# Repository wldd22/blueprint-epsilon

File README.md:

# Epsilon
Columnar split keyboard with 5 columns, 4 rows, and thumb clusters. Made for [Hackclub's Blueprint](https://blueprint.hackclub.com/)

## Details
PCB made using KiCAD \
Case made using Fusion360 \
Firmware made using ZMK

## About
I've always wanted to use a split keyboard, and after making a macropad, I decided the next step was to make a bigger keyboard that could actually replace my regular one for at least some daily use.

## Images

### CAD

### Schematic

### PCB

### Case
| Left Side | Right Side |
|-|-|
|  |  |

## BOM

| Item                                  | Description                                  | Quantity         | Source                                                                                                                                                          | Cost        | Amount                   |
| ------------------------------------- | -------------------------------------------- | ---------------- | --------------------------------------------------------------------------------------------------------------------------------------------------------------- | ----------- | ------------------------ |
| JLC PCB                               | Left and right sides in one piece            | 1                | JLCPCB                                                                                                                                                          | $15.30      | $15.30                   |
| JLC shipping                          | UPS Worldwide Express Saver                  | -                | -                                                                                                                                                               | -           | $15.67                   |
| Case (shipping only)                  | Left and right sides separately              | 2                | Printing Legion                                                                                                                                                 | -           | ~$5                      |
| Kalih Hotswap Sockets                 | Hotswap sockets for Choc V1 switches (x10)   | 5 (44 + 6 extra) | [Chosfox](https://chosfox.com/products/kailh-choc-switch-1350-hot-swap-sockets)                                                                                 | $1.45       | $7.25                    |
| Kailh Choc Low Profile Switches       | Kalih Choc Brown Switches (Tactile) (x10)    | 5 (44 + 6 extra) | [Chosfox](https://chosfox.com/products/kailh-chocs?variant=42514647646402)                                                                                      | $4.5        | $22.50                   |
| Chosfox shipping                      | Standard Shipping China Post                 | -                | -                                                                                                                                                               | -           | $5.20                    |
| CFX Choc Keycaps                      | Chocfox CFX Choc Blank Keycaps (Black) (x10) | 5 (44 + 6 extra) | [NeoMacro](https://typeractive.xyz/products/mbk-keycaps?variant=48512019562727)                                                                                 | ₹350        | ₹1750 (free shipping)    |
| SK6812 MINI-E RGB                     | RGB LEDs (x50)                               | 1 (44 + 6 extra) | [Desertcart](https://www.desertcart.in/products/713547616-50pcs-sk6812-mini-e-rgb-similar-with-ws2812b-sk6812-3228)                                             | ₹1219       | ₹1219 (free shipping)    |
| Seeed Studio XIAO nRF52840            | Microcontroller                              | 2                | [ThinkRobotics](https://thinkrobotics.com/products/seeed-studio-xiao-nrf52840)                                                                                  | ₹1419.93    | ₹2839.86 (free shipping) |
| 1N4148 Diodes                         | 1N4148W SOD-123 Diodes                       | 44               | [Robu](https://robu.in/product/1n4148w-sod-123-1206-diodereel-of-3000/)                                                                                         | ₹0.57 (10+) | ₹25.08                   |
| AC0805FR-072ML-YAGEO                  | 2MΩ Resistor                                 | 2                | [Robu](https://robu.in/product/ac0805fr-072ml-yageo-res-thick-film-0805-2m-ohm-1-0-125w1-8w-%C2%B1100ppm-c-pad-smd-t-r-automotive-aec-q200/)                    | ₹0.64       | ₹1.28                    |
| RT0805FRE071ML-YAGEO                  | 1MΩ Resistor                                 | 2                | [Robu](https://robu.in/product/rt0805fre071ml-yageo-125mw-thin-film-resistor-%C2%B150ppm-%E2%84%83-%C2%B11-1m%CF%89-0805-chip-resistor-surface-mount-rohs/)     | ₹1.38       | ₹2.76                    |
| Battery Jack                          | Black                                        | 2                | [Robu](https://robu.in/product/s2b-ph-klfsn-jst-1x2p-2p-ph-tin-2-25%E2%84%8385%E2%84%83-2a-1-2mm-brass-bend-insert-push-pullp2mm-wire-to-board-connector-rohs/) | ₹13         | ₹26                      |
| LiPo Battery                          | WLY752530 3.7V 500mAh 1S                     | 2                | [Robu](https://robu.in/product/500mah-pcm-protected-micro-li-po-battery/)                                                                                       | ₹261        | ₹522                     |
| Robu shipping                         | Standard Shipping                            | -                | -                                                                                                                                                               | -           | ₹49                      |
| 40x1 Pin 2.54mm Pitch Male Berg Strip | 40pin header                                 | 1                | [Robocraze](https://robocraze.com/products/40x1-pin-2-54mm-pitch-male-berg-strip)                                                                               | ₹6          | ₹6                       |
| Robocraze shipping                    | Standard                                     | -                | -                                                                                                                                                               | -           | ₹49                      |
| M2 Screws                             | Stainless steel, 8mm                         | 4                | [StacksKB](https://stackskb.com/store/m2-screw-8mm-stainless-steel/)                                                                                            | ₹3.10       | ₹12.40                   |
| M2 Hex Nuts                           | Stainless steel                              | 4                | [StacksKB](https://stackskb.com/store/m2-hex-nut-stainless-steel/)                                                                                              | ₹5          | ₹20                      |
| StacksKB shipping                     | Standard                                     | -                | -                                                                                                                                                               | -           | ₹130                     |
| **TOTAL**                             |                                              |                  |                                                                                                                                                                 |             | **~$141**                |

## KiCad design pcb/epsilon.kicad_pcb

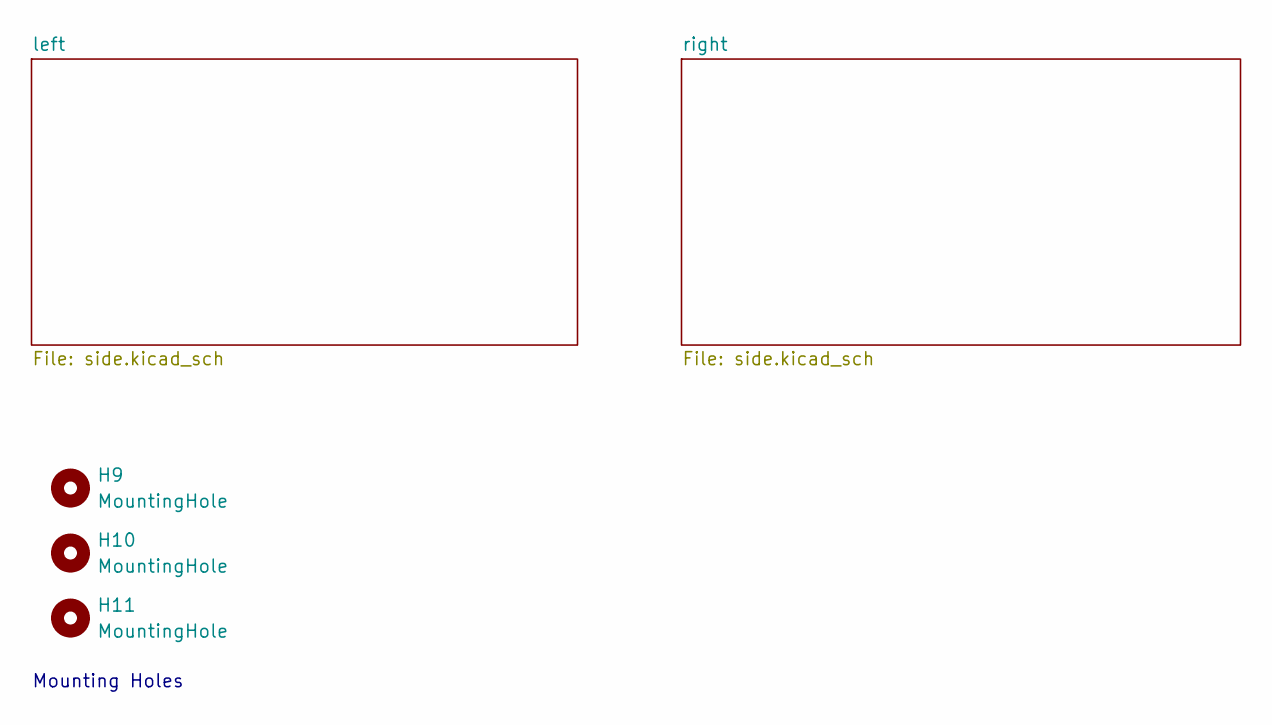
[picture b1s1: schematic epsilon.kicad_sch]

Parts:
H9, H10, H11: MountingHole; MouseBite-Slot_2.0x2.0mm_outset_D0.5mm_P0.85mm_3h

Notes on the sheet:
Mounting Holes

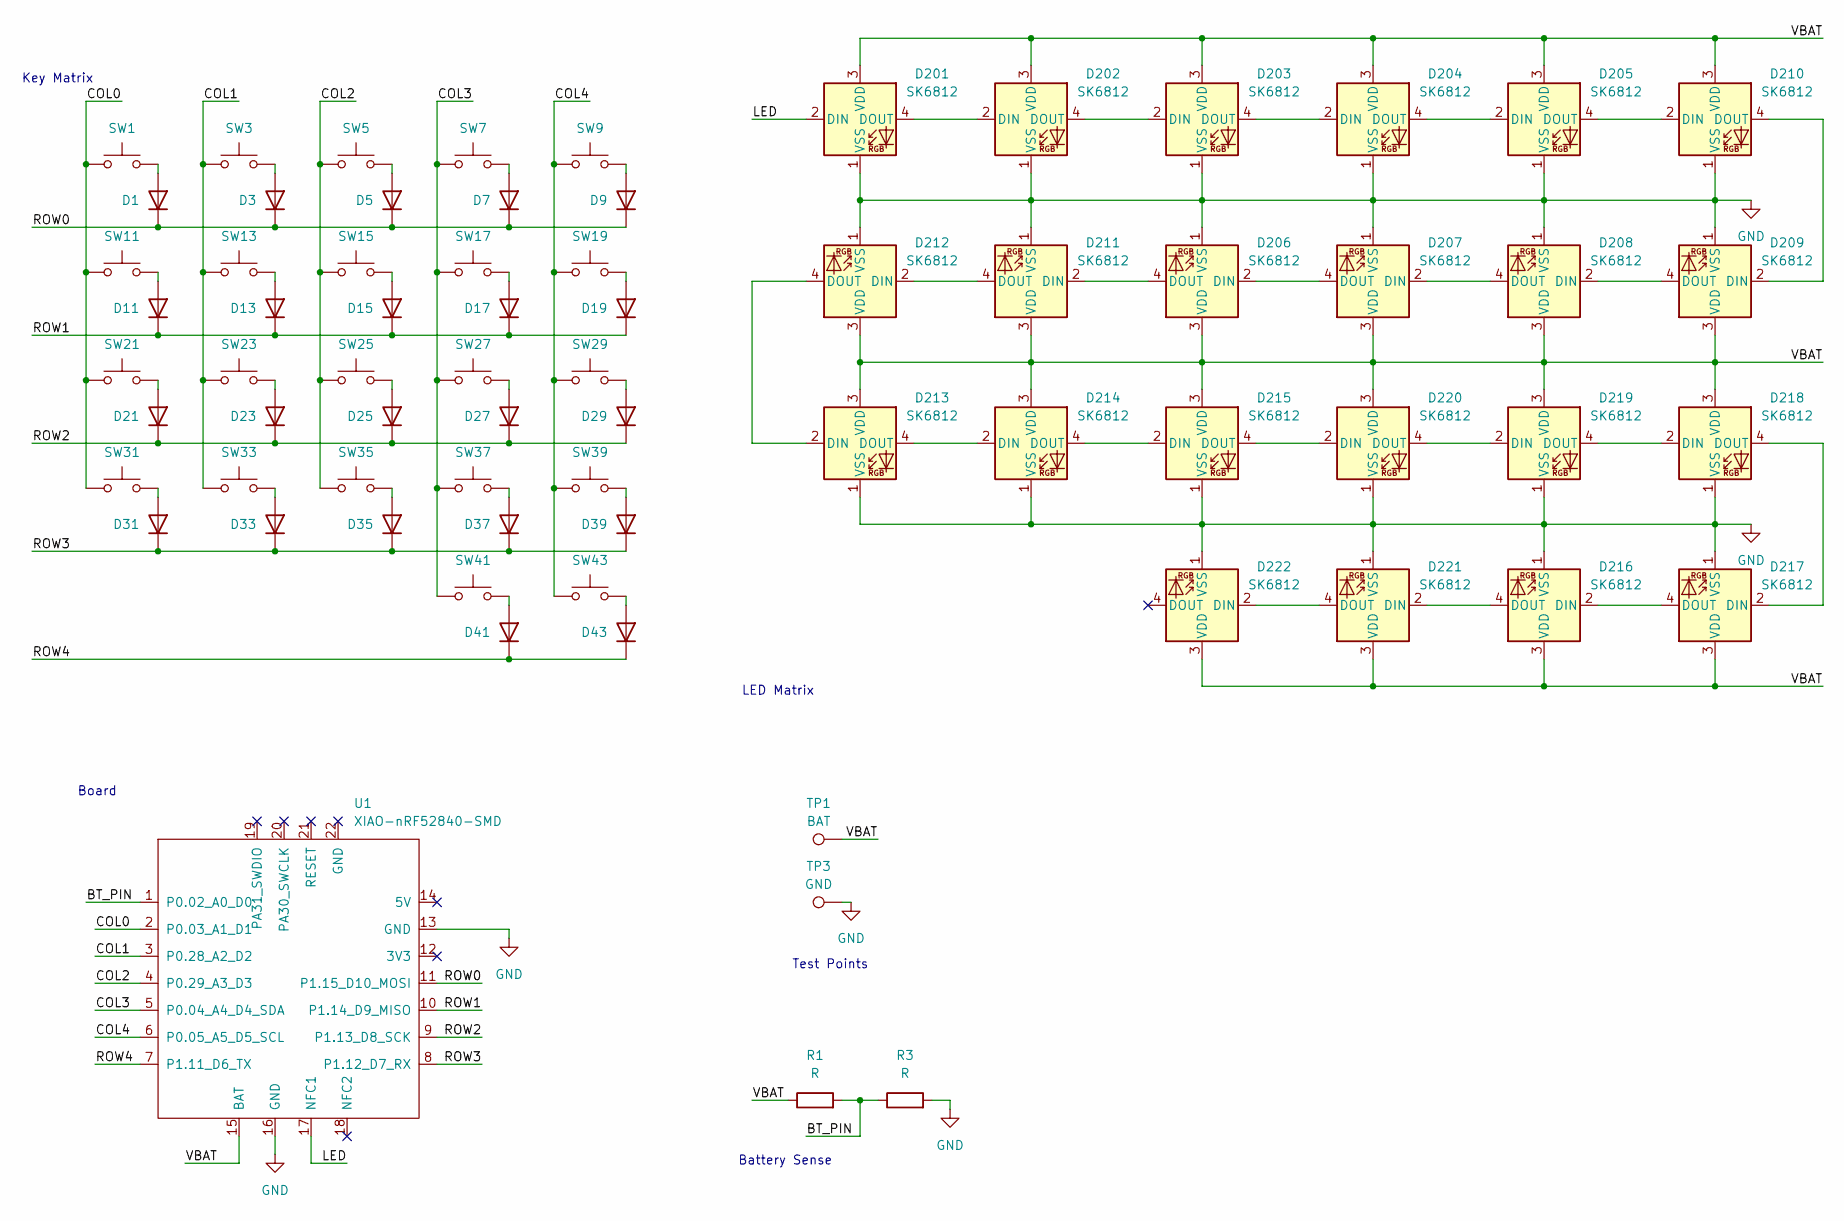
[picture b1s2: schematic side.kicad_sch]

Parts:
D1, D3, D5, D7, D9, D11, D13, D15, D17, D19, D21, D23, D25, D27, D29, D31, D33, D35, D37, D39, D41, D43: D; D_SOD-123
D201, D202, D203, D204, D205, D206, D207, D208, D209, D210, D211, D212, D213, D214, D215, D216, D217, D218, D219, D220, D221, D222: SK6812; LED_choc_6028R
R1, R3: R; R_0805_2012Metric
SW1, SW3, SW5, SW7, SW9, SW11, SW13, SW15, SW17, SW19, SW21, SW23, SW25, SW27, SW29, SW31, SW33, SW35, SW37, SW39, SW41, SW43: SW_Push; SW_choc_v1_HS_CPG135001S30_1u
TP1: BAT; TestPoint_Pad_D2.0mm
TP3: GND; TestPoint_Pad_D2.0mm
U1: XIAO-nRF52840-SMD; modified-XIAO-nRF52840-SMD

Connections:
/left/BT_PIN: R1.2, R3.1, U1.1 (P0.02_A0_D0)
/left/COL0: SW1.1, SW11.1, SW21.1, SW31.1, U1.2 (P0.03_A1_D1)
/left/COL1: SW3.1, SW13.1, SW23.1, SW33.1, U1.3 (P0.28_A2_D2)
/left/COL2: SW5.1, SW15.1, SW25.1, SW35.1, U1.4 (P0.29_A3_D3)
/left/COL3: SW7.1, SW17.1, SW27.1, SW37.1, SW41.1, U1.5 (P0.04_A4_D4_SDA)
/left/COL4: SW9.1, SW19.1, SW29.1, SW39.1, SW43.1, U1.6 (P0.05_A5_D5_SCL)
/left/LED: D201.2 (DIN), U1.17 (NFC1)
/left/ROW0: D1.1 (K), D3.1 (K), D5.1 (K), D7.1 (K), D9.1 (K), U1.11 (P1.15_D10_MOSI)
/left/ROW1: D11.1 (K), D13.1 (K), D15.1 (K), D17.1 (K), D19.1 (K), U1.10 (P1.14_D9_MISO)
/left/ROW2: D21.1 (K), D23.1 (K), D25.1 (K), D27.1 (K), D29.1 (K), U1.9 (P1.13_D8_SCK)
/left/ROW3: D31.1 (K), D33.1 (K), D35.1 (K), D37.1 (K), D39.1 (K), U1.8 (P1.12_D7_RX)
/left/ROW4: D41.1 (K), D43.1 (K), U1.7 (P1.11_D6_TX)
/left/VBAT: D201.3 (VDD), D202.3 (VDD), D203.3 (VDD), D204.3 (VDD), D205.3 (VDD), D206.3 (VDD), D207.3 (VDD), D208.3 (VDD), D209.3 (VDD), D210.3 (VDD), D211.3 (VDD), D212.3 (VDD), D213.3 (VDD), D214.3 (VDD), D215.3 (VDD), D216.3 (VDD), D217.3 (VDD), D218.3 (VDD), D219.3 (VDD), D220.3 (VDD), D221.3 (VDD), D222.3 (VDD), R1.1, TP1.1, U1.15 (BAT)
GND: D201.1 (VSS), D202.1 (VSS), D203.1 (VSS), D204.1 (VSS), D205.1 (VSS), D206.1 (VSS), D207.1 (VSS), D208.1 (VSS), D209.1 (VSS), D210.1 (VSS), D211.1 (VSS), D212.1 (VSS), D213.1 (VSS), D214.1 (VSS), D215.1 (VSS), D216.1 (VSS), D217.1 (VSS), D218.1 (VSS), D219.1 (VSS), D220.1 (VSS), D221.1 (VSS), D222.1 (VSS), R3.2, TP3.1, U1.13 (GND), U1.16 (GND); also elsewhere on the board
unnamed: D1.2 (A), SW1.2
unnamed: D3.2 (A), SW3.2
unnamed: D5.2 (A), SW5.2
unnamed: D7.2 (A), SW7.2
unnamed: D9.2 (A), SW9.2
unnamed: D11.2 (A), SW11.2
unnamed: D13.2 (A), SW13.2
unnamed: D15.2 (A), SW15.2
unnamed: D17.2 (A), SW17.2
unnamed: D19.2 (A), SW19.2
unnamed: D21.2 (A), SW21.2
unnamed: D23.2 (A), SW23.2
unnamed: D25.2 (A), SW25.2
unnamed: D27.2 (A), SW27.2
unnamed: D29.2 (A), SW29.2
unnamed: D31.2 (A), SW31.2
unnamed: D33.2 (A), SW33.2
unnamed: D35.2 (A), SW35.2
unnamed: D37.2 (A), SW37.2
unnamed: D39.2 (A), SW39.2
unnamed: D41.2 (A), SW41.2
unnamed: D43.2 (A), SW43.2
unnamed: D201.4 (DOUT), D202.2 (DIN)
unnamed: D202.4 (DOUT), D203.2 (DIN)
unnamed: D203.4 (DOUT), D204.2 (DIN)
unnamed: D204.4 (DOUT), D205.2 (DIN)
unnamed: D205.4 (DOUT), D210.2 (DIN)
unnamed: D206.2 (DIN), D207.4 (DOUT)
unnamed: D206.4 (DOUT), D211.2 (DIN)
unnamed: D207.2 (DIN), D208.4 (DOUT)
unnamed: D208.2 (DIN), D209.4 (DOUT)
unnamed: D209.2 (DIN), D210.4 (DOUT)
unnamed: D211.4 (DOUT), D212.2 (DIN)
unnamed: D212.4 (DOUT), D213.2 (DIN)
unnamed: D213.4 (DOUT), D214.2 (DIN)
unnamed: D214.4 (DOUT), D215.2 (DIN)
unnamed: D215.4 (DOUT), D220.2 (DIN)
unnamed: D216.2 (DIN), D217.4 (DOUT)
unnamed: D216.4 (DOUT), D221.2 (DIN)
unnamed: D217.2 (DIN), D218.4 (DOUT)
unnamed: D218.2 (DIN), D219.4 (DOUT)
unnamed: D219.2 (DIN), D220.4 (DOUT)
unnamed: D221.4 (DOUT), D222.2 (DIN)

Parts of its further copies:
D2, D4, D6, D8, D10, D12, D14, D16, D18, D20, D22, D24, D26, D28, D30, D32, D34, D36, D38, D40, D42, D44: D; D_SOD-123
D301, D302, D303, D304, D305, D306, D307, D308, D309, D310, D311, D312, D313, D314, D315, D316, D317, D318, D319, D320, D321, D322: SK6812; LED_choc_6028R
R2, R4: R; R_0805_2012Metric
SW2, SW4, SW6, SW8, SW10, SW12, SW14, SW16, SW18, SW20, SW22, SW24, SW26, SW28, SW30, SW32, SW34, SW36, SW38, SW40, SW42, SW44: SW_Push; SW_choc_v1_HS_CPG135001S30_1u
TP2: BAT; TestPoint_Pad_D2.0mm
TP4: GND; TestPoint_Pad_D2.0mm
U2: XIAO-nRF52840-SMD; modified-XIAO-nRF52840-SMD

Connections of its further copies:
/right/BT_PIN: R2.2, R4.1, U2.1 (P0.02_A0_D0)
/right/COL0: SW2.1, SW12.1, SW22.1, SW32.1, U2.2 (P0.03_A1_D1)
/right/COL1: SW4.1, SW14.1, SW24.1, SW34.1, U2.3 (P0.28_A2_D2)
/right/COL2: SW6.1, SW16.1, SW26.1, SW36.1, U2.4 (P0.29_A3_D3)
/right/COL3: SW8.1, SW18.1, SW28.1, SW38.1, SW42.1, U2.5 (P0.04_A4_D4_SDA)
/right/COL4: SW10.1, SW20.1, SW30.1, SW40.1, SW44.1, U2.6 (P0.05_A5_D5_SCL)
/right/LED: D301.2 (DIN), U2.17 (NFC1)
/right/ROW0: D2.1 (K), D4.1 (K), D6.1 (K), D8.1 (K), D10.1 (K), U2.11 (P1.15_D10_MOSI)
/right/ROW1: D12.1 (K), D14.1 (K), D16.1 (K), D18.1 (K), D20.1 (K), U2.10 (P1.14_D9_MISO)
/right/ROW2: D22.1 (K), D24.1 (K), D26.1 (K), D28.1 (K), D30.1 (K), U2.9 (P1.13_D8_SCK)
/right/ROW3: D32.1 (K), D34.1 (K), D36.1 (K), D38.1 (K), D40.1 (K), U2.8 (P1.12_D7_RX)
/right/ROW4: D42.1 (K), D44.1 (K), U2.7 (P1.11_D6_TX)
/right/VBAT: D301.3 (VDD), D302.3 (VDD), D303.3 (VDD), D304.3 (VDD), D305.3 (VDD), D306.3 (VDD), D307.3 (VDD), D308.3 (VDD), D309.3 (VDD), D310.3 (VDD), D311.3 (VDD), D312.3 (VDD), D313.3 (VDD), D314.3 (VDD), D315.3 (VDD), D316.3 (VDD), D317.3 (VDD), D318.3 (VDD), D319.3 (VDD), D320.3 (VDD), D321.3 (VDD), D322.3 (VDD), R2.1, TP2.1, U2.15 (BAT)
GND: D301.1 (VSS), D302.1 (VSS), D303.1 (VSS), D304.1 (VSS), D305.1 (VSS), D306.1 (VSS), D307.1 (VSS), D308.1 (VSS), D309.1 (VSS), D310.1 (VSS), D311.1 (VSS), D312.1 (VSS), D313.1 (VSS), D314.1 (VSS), D315.1 (VSS), D316.1 (VSS), D317.1 (VSS), D318.1 (VSS), D319.1 (VSS), D320.1 (VSS), D321.1 (VSS), D322.1 (VSS), R4.2, TP4.1, U2.13 (GND), U2.16 (GND); also elsewhere on the board
unnamed: D2.2 (A), SW2.2
unnamed: D4.2 (A), SW4.2
unnamed: D6.2 (A), SW6.2
unnamed: D8.2 (A), SW8.2
unnamed: D10.2 (A), SW10.2
unnamed: D12.2 (A), SW12.2
unnamed: D14.2 (A), SW14.2
unnamed: D16.2 (A), SW16.2
unnamed: D18.2 (A), SW18.2
unnamed: D20.2 (A), SW20.2
unnamed: D22.2 (A), SW22.2
unnamed: D24.2 (A), SW24.2
unnamed: D26.2 (A), SW26.2
unnamed: D28.2 (A), SW28.2
unnamed: D30.2 (A), SW30.2
unnamed: D32.2 (A), SW32.2
unnamed: D34.2 (A), SW34.2
unnamed: D36.2 (A), SW36.2
unnamed: D38.2 (A), SW38.2
unnamed: D40.2 (A), SW40.2
unnamed: D42.2 (A), SW42.2
unnamed: D44.2 (A), SW44.2
unnamed: D301.4 (DOUT), D302.2 (DIN)
unnamed: D302.4 (DOUT), D303.2 (DIN)
unnamed: D303.4 (DOUT), D304.2 (DIN)
unnamed: D304.4 (DOUT), D305.2 (DIN)
unnamed: D305.4 (DOUT), D310.2 (DIN)
unnamed: D306.2 (DIN), D307.4 (DOUT)
unnamed: D306.4 (DOUT), D311.2 (DIN)
unnamed: D307.2 (DIN), D308.4 (DOUT)
unnamed: D308.2 (DIN), D309.4 (DOUT)
unnamed: D309.2 (DIN), D310.4 (DOUT)
unnamed: D311.4 (DOUT), D312.2 (DIN)
unnamed: D312.4 (DOUT), D313.2 (DIN)
unnamed: D313.4 (DOUT), D314.2 (DIN)
unnamed: D314.4 (DOUT), D315.2 (DIN)
unnamed: D315.4 (DOUT), D320.2 (DIN)
unnamed: D316.2 (DIN), D317.4 (DOUT)
unnamed: D316.4 (DOUT), D321.2 (DIN)
unnamed: D317.2 (DIN), D318.4 (DOUT)
unnamed: D318.2 (DIN), D319.4 (DOUT)
unnamed: D319.2 (DIN), D320.4 (DOUT)
unnamed: D321.4 (DOUT), D322.2 (DIN)

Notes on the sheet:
Battery Sense
Test Points
Board
LED Matrix
Key Matrix

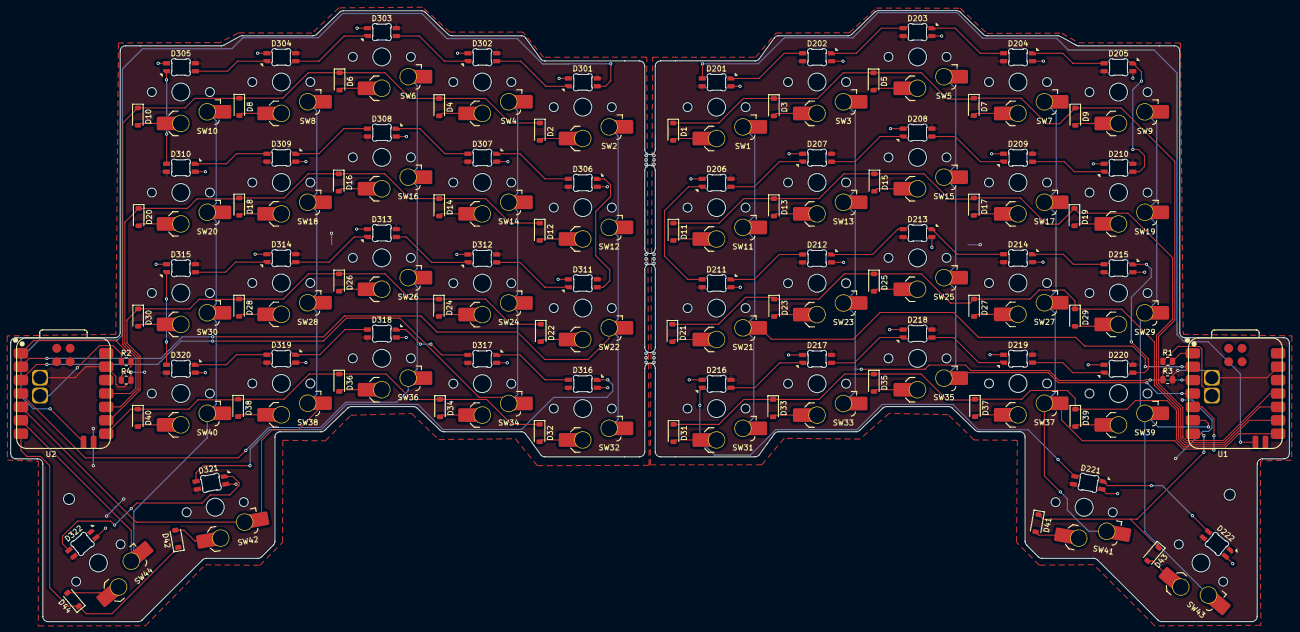
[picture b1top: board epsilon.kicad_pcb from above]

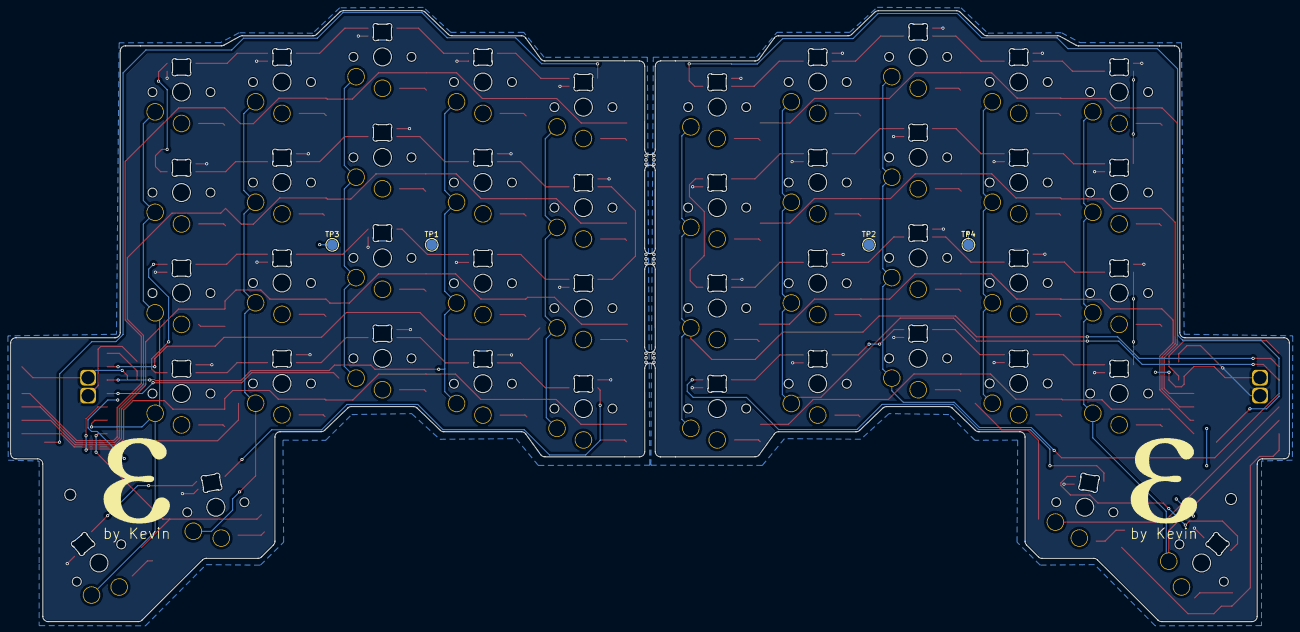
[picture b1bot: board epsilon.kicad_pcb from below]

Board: 2 copper layers, 242.4 x 115.8 mm, 145 parts (4 on the bottom side), 113 nets.

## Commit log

2026-02-08 Add .gitignore
2026-02-09 Finished schematic, started layout
2026-02-09 Added LEDs to schematic, updated layout
2026-02-13 Finish layout (mostly), route components
2026-02-14 Add left side and mousebites
2026-02-14 Add logo and tag
2026-02-15 Add User.1, User.2, and User.3 layers
2026-02-28 Update User layers
2026-03-29 Add mounting holes in PCB
2026-03-29 Add gerbers
2026-03-29 Add images
2026-03-29 Add steps
2026-03-31 Add BOM
2026-03-31 Modify PCB
2026-03-31 Add test firmware
2026-04-02 Optimise BOM and add shipping costs
2026-04-02 Optimise BOM further
2026-04-02 Add PCB models
2026-04-02 Add case tops
2026-04-02 Add CAD image
2026-04-02 Add CAD files
